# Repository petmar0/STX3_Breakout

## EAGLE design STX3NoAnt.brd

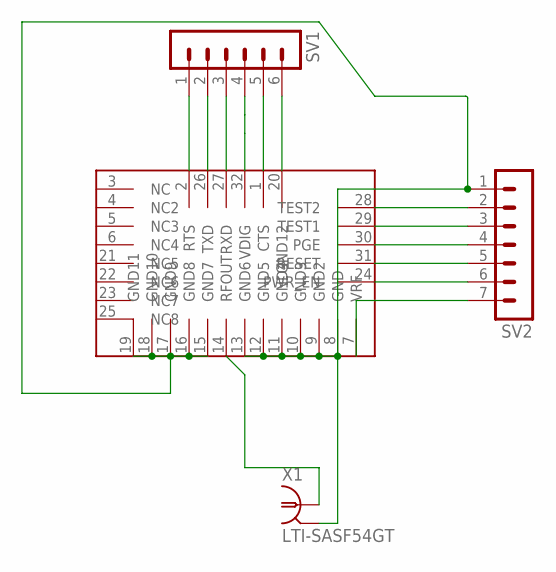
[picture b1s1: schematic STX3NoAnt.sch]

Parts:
SV1: MA06-1
SV2: MA07-1
U$1: STX3
X1: LTI-SASF54GT

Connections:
unnamed: SV1.4, U$1.32 (VDIG)
unnamed: SV1.2, U$1.26 (TXD)
unnamed: SV1.3, U$1.27 (RXD)
unnamed: SV1.1, U$1.2 (RTS)
unnamed: SV1.6, U$1.20 (GND12)
unnamed: SV2.2, U$1.28 (TEST2)
unnamed: SV1.5, U$1.1 (CTS)
unnamed: SV2.3, U$1.29 (TEST1)
unnamed: SV2.4, U$1.30 (PGE)
unnamed: SV2.5, U$1.31 (RESET)
unnamed: SV2.6, U$1.24 (PWR_EN)
unnamed: SV2.7, U$1.7 (VRF)
unnamed: SV2.1, U$1.8 (GND), U$1.9 (GND2), U$1.10 (GND3), U$1.11 (GND4), U$1.12 (GND5), U$1.13 (GND6), U$1.15 (GND7), U$1.16 (GND8), U$1.17 (GND9), U$1.18 (GND10), U$1.19 (GND11), X1.2, X1.3 (2), X1.4 (2), X1.5 (2)
unnamed: U$1.14 (RFOUT), X1.1

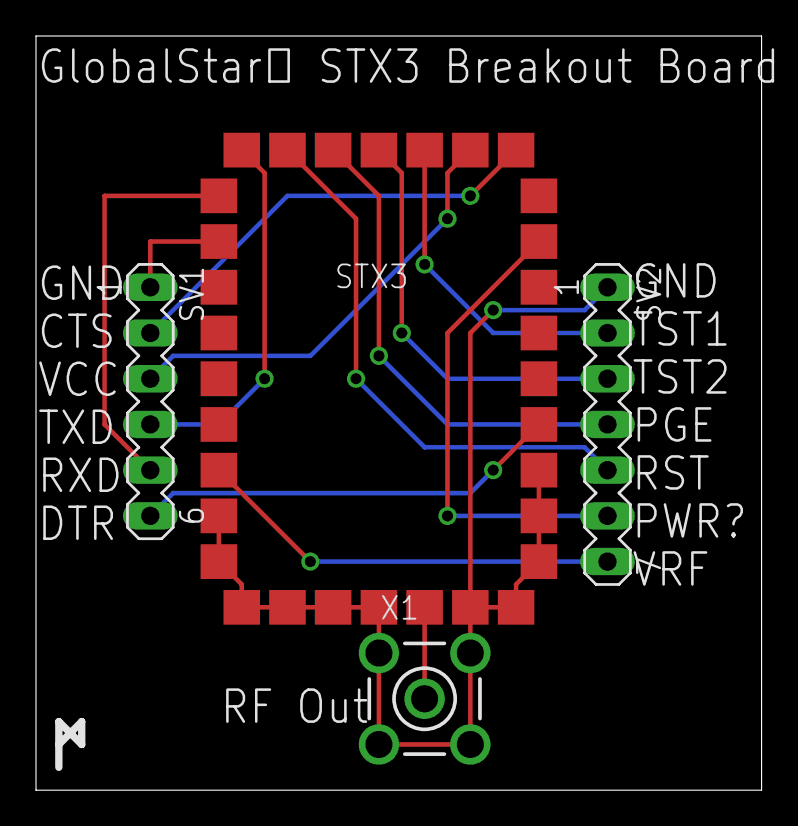
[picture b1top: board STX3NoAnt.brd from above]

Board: 2 copper layers, 40.3 x 41.9 mm, 4 parts (0 on the bottom side), 14 nets.

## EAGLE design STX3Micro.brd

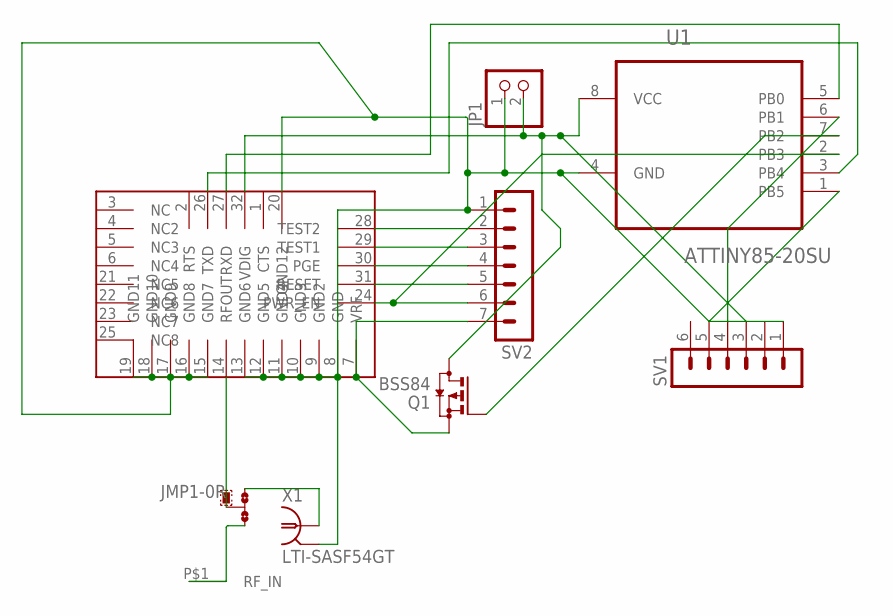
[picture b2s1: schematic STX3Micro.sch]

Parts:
JMP1: 0R-JUMPC; C0R-JMP
JP1: PINHD-1X2; 1X02
Q1: BSS84; SOT23
SV1: MA06-1
SV2: MA07-1
U1: ATTINY85-20SU; SOIC127P798X216-8N
U$1: STX3
U$2: GSANTENNA
X1: LTI-SASF54GT

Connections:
unnamed: SV1.5, U1.1 (PB5)
unnamed: U1.3 (PB4), U$1.26 (TXD)
unnamed: U1.5 (PB0), U$1.27 (RXD)
unnamed: JP1.2, Q1.3 (D), SV1.3, U1.8 (VCC), U$1.32 (VDIG)
unnamed: SV1.4, U1.6 (PB1)
unnamed: SV2.2, U$1.28 (TEST2)
unnamed: JMP1.2, U$1.14 (RFOUT)
unnamed: JMP1.3, U$2.P$1
unnamed: SV2.3, U$1.29 (TEST1)
unnamed: SV2.4, U$1.30 (PGE)
unnamed: SV2.5, U$1.31 (RESET)
unnamed: SV2.6, U1.2 (PB3), U$1.24 (PWR_EN)
unnamed: Q1.2 (S), SV2.7, U$1.7 (VRF)
unnamed: JP1.1, SV1.1, SV2.1, U1.4 (GND), U$1.8 (GND), U$1.9 (GND2), U$1.10 (GND3), U$1.11 (GND4), U$1.12 (GND5), U$1.13 (GND6), U$1.15 (GND7), U$1.16 (GND8), U$1.17 (GND9), U$1.18 (GND10), U$1.19 (GND11), U$1.20 (GND12), X1.2, X1.3 (2), X1.4 (2), X1.5 (2)
unnamed: JMP1.1, X1.1
unnamed: Q1.1 (G), U1.7 (PB2)
unnamed: SV1.6, U$1.2 (RTS)
unnamed: SV1.2, U$1.1 (CTS)

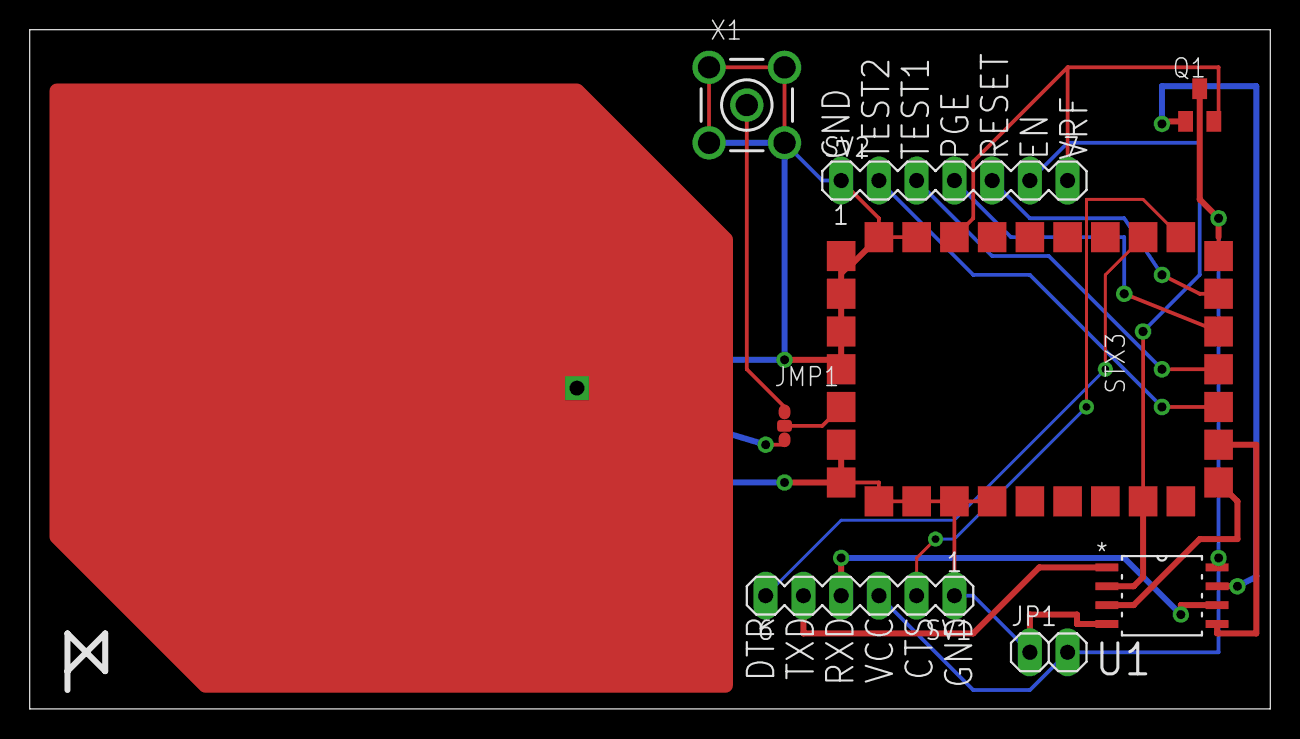
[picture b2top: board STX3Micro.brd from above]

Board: 2 copper layers, 83.5 x 45.7 mm, 9 parts (0 on the bottom side), 18 nets.

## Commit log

2014-07-21 Fixed Feed Point
2014-07-21 Fixed Via Concentricity
2014-07-28 Micro Board Routing Done
2014-07-28 Fixed Ground Loop
2014-07-28 Design Check
2014-07-28 Fixed CTS/RTS Connections
2014-08-08 Created NoAntenna Version
